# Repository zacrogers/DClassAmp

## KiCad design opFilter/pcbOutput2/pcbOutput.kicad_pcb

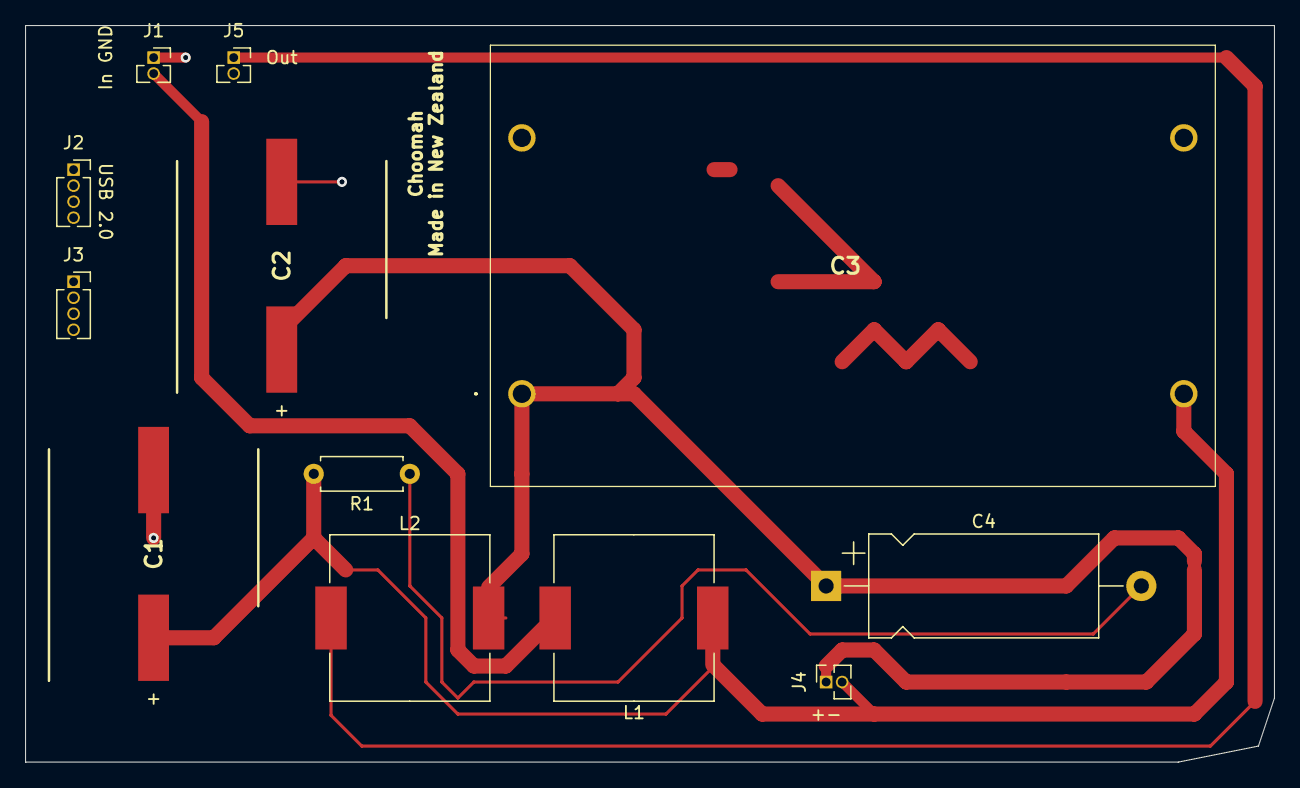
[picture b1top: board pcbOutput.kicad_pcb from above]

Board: 2 copper layers, 99.1 x 58.4 mm, 12 parts (0 on the bottom side), 6 nets.

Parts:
C1, C2: 18 uF; CAPAE1660X1750N
C3: 130 uF; C4AQLBW6130A3NK
C4: 10 nF; CP_Axial_L18.0mm_D8.0mm_P25.00mm_Horizontal
J1, J4, J5: Conn_01x02_Female; PinSocket_1x02_P1.27mm_Vertical
J2, J3: Conn_01x04_Female; PinSocket_1x04_P1.27mm_Vertical
L1, L2: 1.1 mH; L_Wuerth_HCM-1390
R1: 4; R_Axial_DIN0207_L6.3mm_D2.5mm_P7.62mm_Horizontal

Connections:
GND: C1.2, C2.2, J1.1
unnamed: C1.1, C3.2, J4.2, L1.1, R1.2
unnamed: C2.1, C3.1, C4.1, J4.1, L2.2
unnamed: C4.2, R1.1
unnamed: J1.2, L1.2
unnamed: J5.1, L2.1

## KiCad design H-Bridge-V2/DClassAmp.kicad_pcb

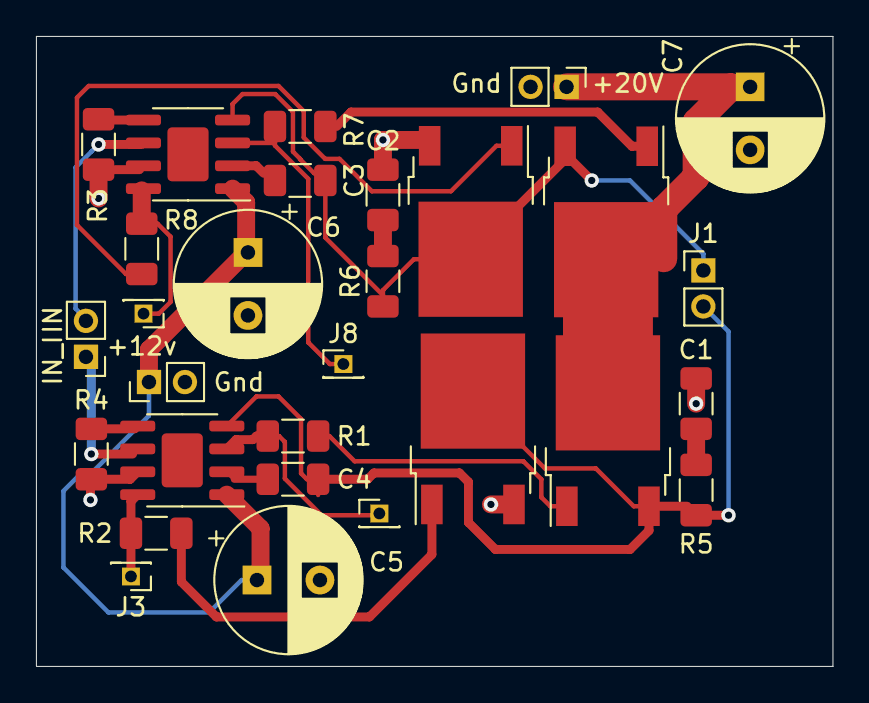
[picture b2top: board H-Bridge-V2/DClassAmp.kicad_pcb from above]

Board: 2 copper layers, 44.2 x 35.0 mm, 29 parts (0 on the bottom side), 21 nets.

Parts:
C1, C2: C; C_1206_3216Metric
C3, C4: CP; C_1206_3216Metric
C5, C6, C7: C; CP_Radial_D8.0mm_P3.50mm
J1: ToFilterConnector; PinHeader_1x02_P2.00mm_Vertical
J2: PWMInputConnector; PinHeader_1x02_P2.00mm_Vertical
J3, J6, J7, J8: Conn_01x01_Male; PinHeader_1x01_P1.27mm_Vertical
J4: +12VConnector; PinHeader_1x02_P2.00mm_Vertical
J5: +24VConnector; PinHeader_1x02_P2.00mm_Vertical
Q1, Q2, Q3, Q4: RFD16N05; TO-252-2
R1, R2, R3, R4, R5, R6, R7, R8: R; R_1206_3216Metric
U1, U2: LM5104M; SOIC-8-1EP_3.9x4.9mm_P1.27mm_EP2.29x3mm

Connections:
+12V: C5.1, C6.1, J4.1, U1.1, U2.1
+24V: C7.1, J5.1, Q1.2, Q3.2
AHO: J8.1, R7.1, U1.3
AHS: C3.2, J1.1, Q3.3, Q4.2, R6.1, U1.4
ALO: J7.1, R8.1, U1.8
BHO: J6.1, R1.2, U2.3
BHS: C4.2, J1.2, Q1.3, Q2.2, R5.1, U2.4
BLO: J3.1, R2.2, U2.8
GND: C1.2, C2.2, C5.2, C6.2, C7.2, J4.2, J5.2, Q2.3, Q4.3, R3.2, R4.2, U1.7, U2.7
unnamed: C1.1, R5.2
unnamed: C2.1, R6.2
unnamed: C3.1, U1.2
unnamed: C4.1, U2.2
unnamed: Q1.1, R1.1
unnamed: Q2.1, R2.1
unnamed: Q3.1, R7.2
unnamed: Q4.1, R8.2
unnamed: R3.1, U1.5
unnamed: R4.1, U2.5
PWM: J2.2, U1.6
PWMInv: J2.1, U2.6

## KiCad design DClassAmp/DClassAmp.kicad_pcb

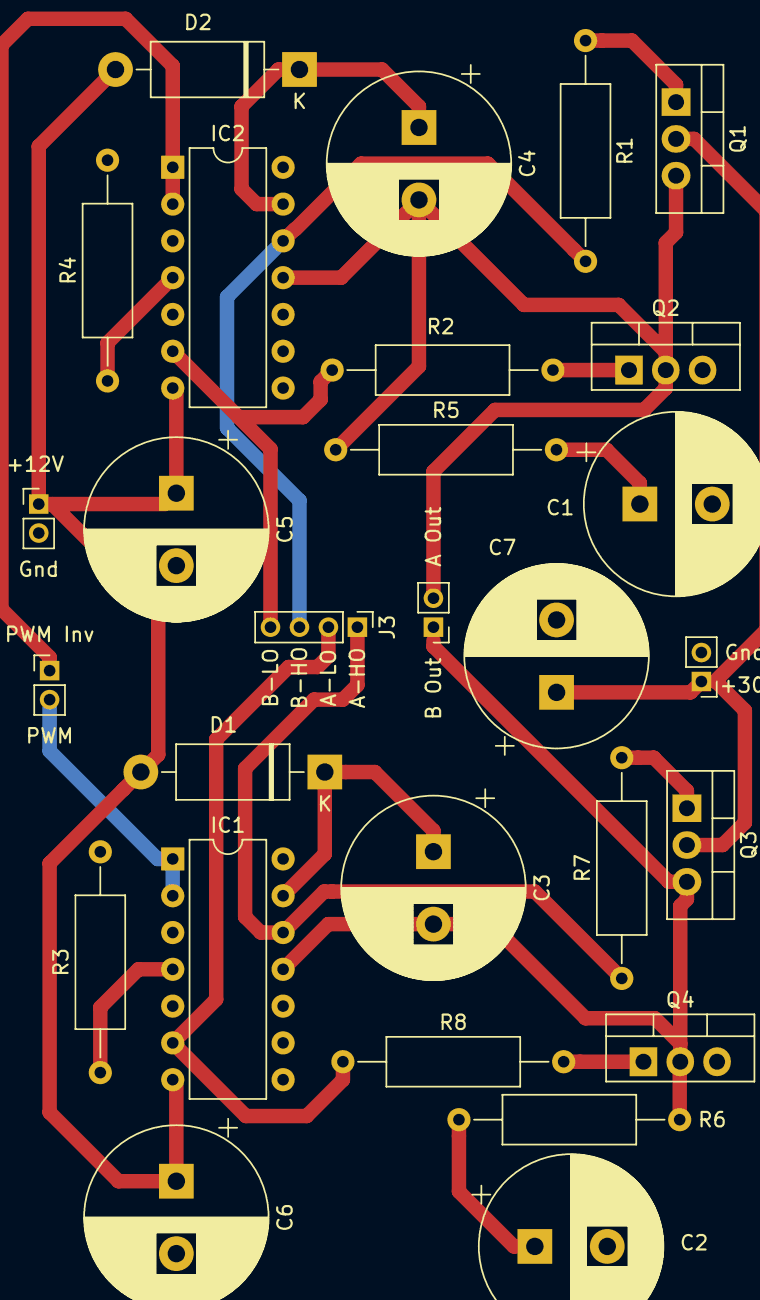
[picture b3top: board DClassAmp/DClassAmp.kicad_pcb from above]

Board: 2 copper layers, 28 parts (0 on the bottom side), 21 nets.

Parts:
C1, C2, C3, C4, C5, C6, C7: C; CP_Radial_D12.5mm_P5.00mm
D1, D2: D; D_DO-15_P12.70mm_Horizontal
IC1, IC2: IR21834PBF; DIP-14_W7.62mm
J1: ToFilterConnector; PinHeader_1x02_P2.00mm_Vertical
J2: PWMInputConnector; PinHeader_1x02_P2.00mm_Vertical
J3: MosfetGateTestpoints; PinHeader_1x04_P2.00mm_Vertical
J4: +12VConnector; PinHeader_1x02_P2.00mm_Vertical
J5: +24VConnector; PinHeader_1x02_P2.00mm_Vertical
Q1, Q2, Q3, Q4: IRF540N; TO-220-3_Vertical
R1, R2, R3, R4, R5, R6, R7, R8: R; R_Axial_DIN0309_L9.0mm_D3.2mm_P15.24mm_Horizontal

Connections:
+12V: C5.1, C6.1, D1.2, D2.2, IC1.7, IC2.7, J4.1
+24V: C7.1, J5.1, Q1.2, Q3.2
AHO: IC1.12, J3.1, R7.1
ALO: IC1.6, J3.2, R8.1
AVS: C3.2, IC1.11, J1.1, Q3.3, Q4.2, R6.1
BHO: IC2.12, J3.3, R1.2
BLO: IC2.6, J3.4, R2.2
BVS: C4.2, IC2.11, J1.2, Q1.3, Q2.2, R5.1
GND: C1.2, C2.2, C5.2, C6.2, C7.2, IC1.3, IC1.5, IC2.3, IC2.5, J4.2, J5.2, Q2.3, Q4.3, R3.2, R4.2
unnamed: C1.1, R5.2
unnamed: C2.1, R6.2
unnamed: C3.1, D1.1, IC1.13
unnamed: C4.1, D2.1, IC2.13
unnamed: IC1.4, R3.1
unnamed: IC2.4, R4.1
unnamed: Q1.1, R1.1
unnamed: Q2.1, R2.1
unnamed: Q3.1, R7.2
unnamed: Q4.1, R8.2
PWM: IC1.1, IC1.2, J2.2
PWMInv: IC2.1, IC2.2, J2.1

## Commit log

2021-07-24 Started h bridge circuit
2021-07-25 Added spice sim
2021-07-29 Added h bridge v2
2021-07-29 Added connector to h bridge schematic
2021-08-02 Added snubber cicuit
2021-08-03 Added h bridge pcb
2021-08-05 Added h bridge PCB image
2021-08-11 Update Sim Files(output)
2021-08-11 Added smd hbridge pcb
2021-08-12 updated sim files
2021-08-13 submission
